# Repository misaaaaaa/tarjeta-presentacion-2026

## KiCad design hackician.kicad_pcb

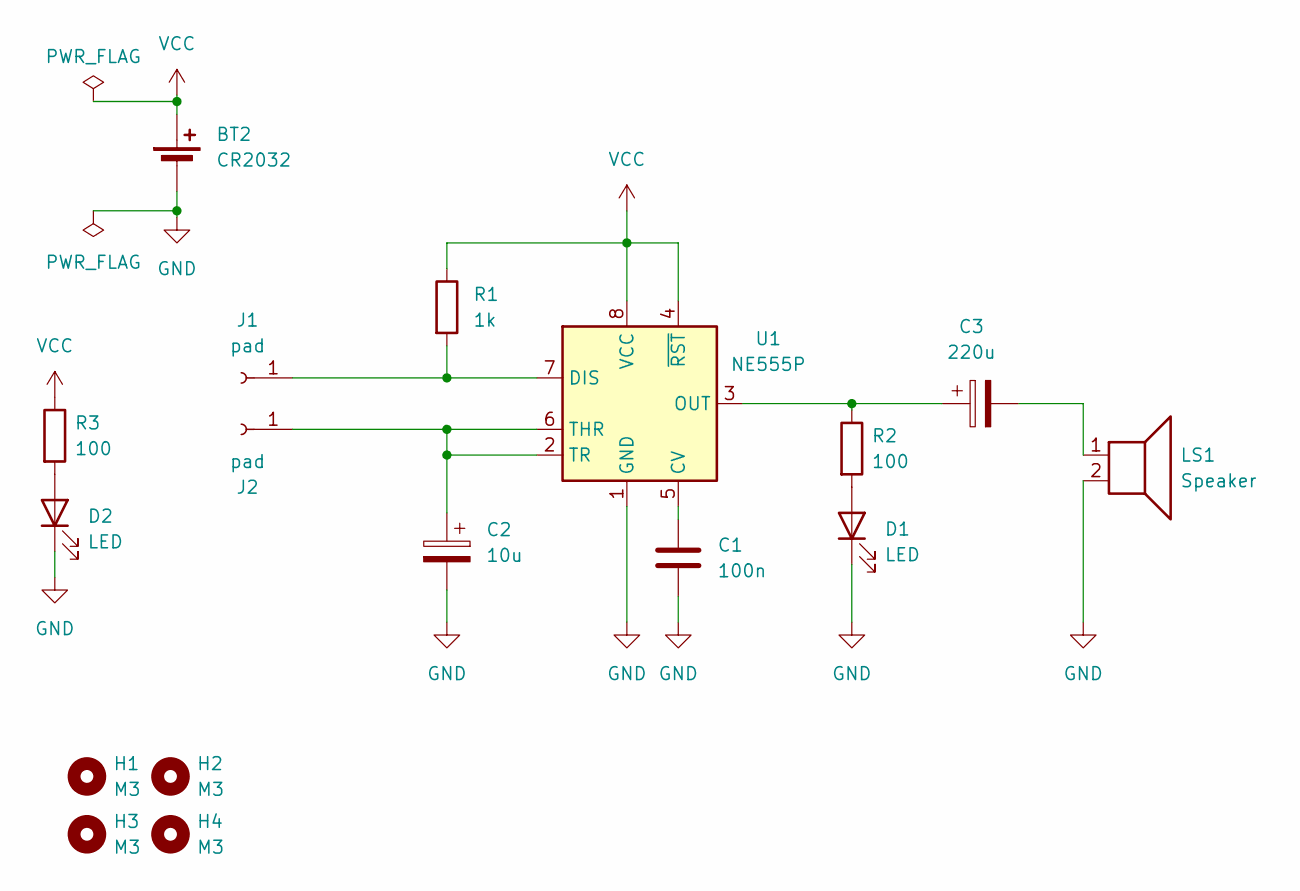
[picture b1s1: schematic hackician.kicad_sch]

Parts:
BT2: CR2032; BatteryHolder_MYOUNG_BS-07-A1BJ001_CR2032
C1: 100n; C_Disc_D3.4mm_W2.1mm_P2.50mm
C2: 10u; CP_Radial_D4.0mm_P2.00mm
C3: 220u; CP_Radial_D6.3mm_P2.50mm
D1, D2: LED; LED_PCBasDiffuser
H1, H2, H3, H4: M3; MountingHole_3.2mm_M3
J1, J2: pad; TestPoint_Pad_D4.0mm
LS1: Speaker; SolderWire-0.25sqmm_1x02_P4.5mm_D0.65mm_OD2mm_Relief
R1: 1k; R_0805_2012Metric_Pad1.20x1.40mm_HandSolder
R2, R3: 100; R_0805_2012Metric_Pad1.20x1.40mm_HandSolder
U1: NE555P; SOIC-8_3.9x4.9mm_P1.27mm

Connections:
GND: BT2.2 (-), C1.2, C2.2, D1.1 (K), D2.1 (K), LS1.2, U1.1 (GND)
unnamed: C3.2, LS1.1
unnamed: D1.2 (A), R2.2
unnamed: D2.2 (A), R3.2
unnamed: J1.1 (Pin_1_1), R1.2, U1.7 (DIS)
unnamed: C2.1, J2.1 (Pin_1_1), U1.2 (TR), U1.6 (THR)
unnamed: C1.1, U1.5 (CV)
unnamed: C3.1, R2.1, U1.3 (OUT)
VCC: BT2.1 (+), R1.1, R3.1, U1.4 (~RST), U1.8 (VCC)

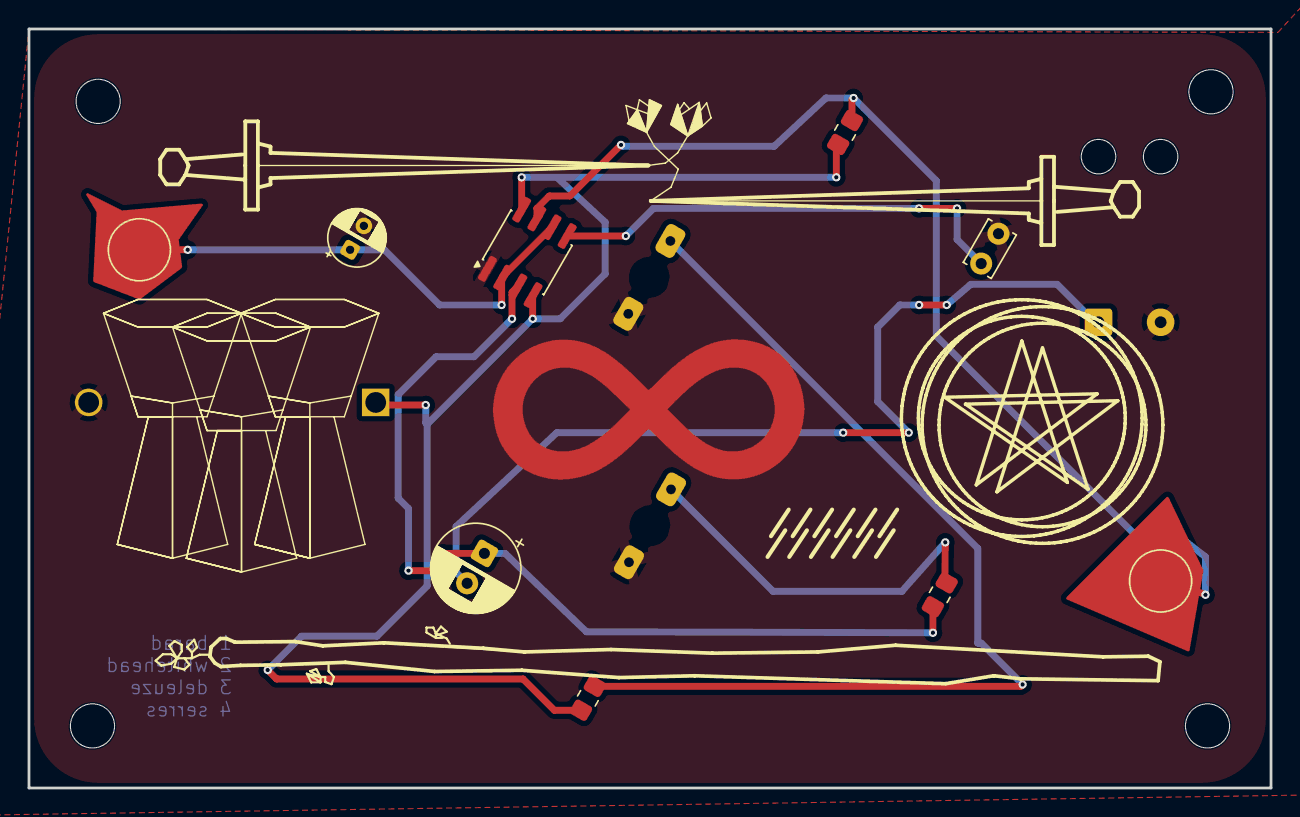
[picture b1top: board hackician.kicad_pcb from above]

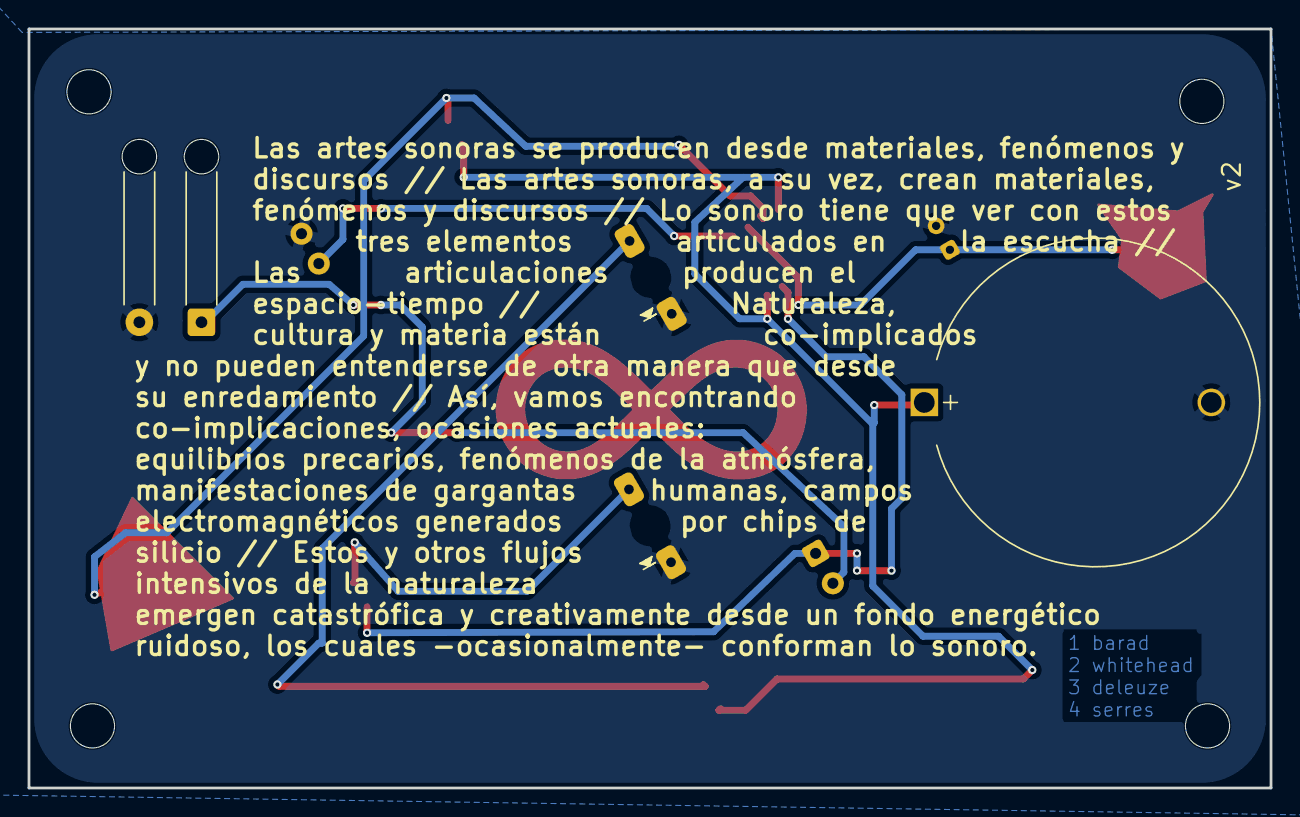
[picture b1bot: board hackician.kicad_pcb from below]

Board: 2 copper layers, 90.0 x 55.0 mm, 17 parts (2 on the bottom side), 9 nets.
